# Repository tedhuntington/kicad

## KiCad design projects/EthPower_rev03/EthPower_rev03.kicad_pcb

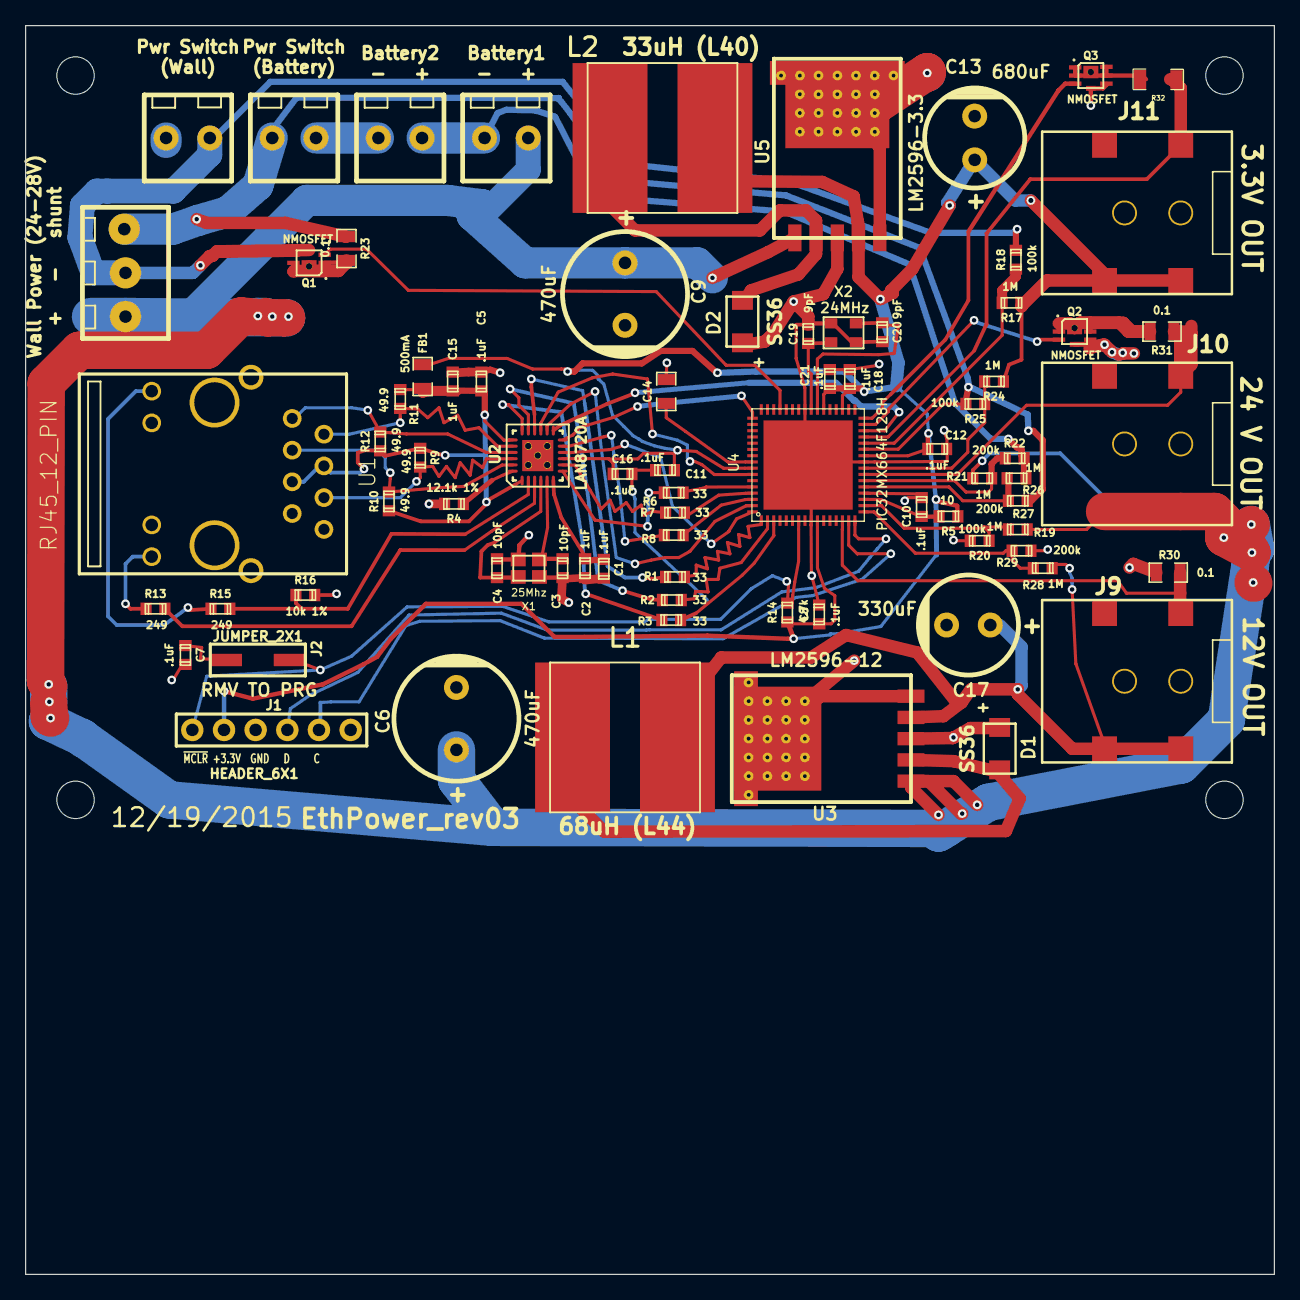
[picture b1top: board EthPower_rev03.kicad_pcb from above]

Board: 2 copper layers, 100.0 x 100.0 mm, 82 parts (0 on the bottom side), 63 nets.

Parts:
C1, C5, C7, C8, C10, C11, C12, C16, C18, C21: .1uF; TED_SM0603_C
C2, C15: 1uF; TED_SM0603_C
C3, C4: 10pF; TED_SM0603_C
C6, C9: 470uF; TED_c_elec_radial_10mm
C13: 680uF; TED_c_elec_radial_8mm
C14: 10uF (low ESR 1ohm); TED_SM0805_C
C17: 330uF; TED_c_elec_radial_8mm
C19, C20: 9pF; TED_SM0603_C
D1, D2: SS36; TED_DO-214AC
FB1: 500mA; TED_SM0805_R
H1, H2, H3, H4: HOLE; TED_Hole_3mm
J1: HEADER_6X1; TED_HEADER_6x1
J2: JUMPER_2X1; TED_HEADER_2x1_SMT
J3, J5, J6, J7: TERMINAL_2X1; TED_TERMINAL_3.5MM_2PIN
J8: TERMINAL_3X1; TED_TERMINAL_3.5MM_3PIN
J9, J10, J11: DC_2.1MM; TED_2.1mm_DC_SMD
L1: 68uH (L44); INDUCTOR_12x12_SMD
L2: 33uH (L40); INDUCTOR_12x12_SMD
Q1, Q2, Q3: NMOSFET; TED_PQFN6+1
R1, R2, R3, R6, R7, R8: 33; TED_SM0603_R
R4: 12.1k 1%; TED_SM0603_R
R5: 10; TED_SM0603_R
R9, R10, R11, R12: 49.9; TED_SM0603_R
R13, R15: 249; TED_SM0603_R
R14: 4.7k; TED_SM0603_R
R16: 10k 1%; TED_SM0603_R
R17, R19, R21, R24, R26, R28: 1M; TED_SM0603_R
R18, R20, R25: 100k; TED_SM0603_R
R22, R27, R29: 200k; TED_SM0603_R
R23, R30, R31: 0.1; TED_SM0805_R
R32: 0.1; TED_SM1206_R
U1: RJ45_12_PIN; TED_RJ45_12pin_Top
U2: LAN8720A; TED_QFN24+1
U3: LM2596-12; TED_TO263
U4: PIC32MX664F128H; TED_QFN64+1
U5: LM2596-3.3; TED_TO263
X1: 25Mhz; TED_crystal_FA-20H
X2: 24MHz; crystal_TSX3225

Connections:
12V: C17.1, J9.1, L1.2, R28.1, U3.4
AVDD: C5.1, C15.1, FB1.2, R9.1, R10.1, R11.1, R12.1, U1.4, U1.5, U2.1, U2.19
ECRSDV: R8.2, U4.62
EMDC: U2.13, U4.30
EMDIO: U2.12, U4.49
EREFCLK: U2.14, U4.63
ERXD0: R7.2, U4.61
ERXD1: R6.2, U4.60
ERXERR: U2.10, U4.64
ETXD0: R2.2, U4.2
ETXD1: R3.2, U4.3
ETXEN: R1.2, U4.1
GND: C1.2, C2.2, C3.2, C4.1, C5.2, C6.2, C7.2, C8.2, C9.2, C10.2, C11.2, C12.2, C13.2, C14.2, C15.2, C16.2, C17.2, C18.2, C19.2, C20.2, C21.2, D1.2, D2.2, J1.3, J5.1, Q2.2, Q3.2, R4.2, R16.2, R20.2, R29.2, R30.2, U1.8, U1.10, U1.11, U2.25, U3.3, U3.5, U4.9, U4.20, U4.25, U4.41, U4.65, U5.3, U5.5, X1.2, X1.4, X2.2, X2.4
GNDWALL: J5.2, J8.2, Q1.2, R18.2
GreenLED: R15.1, U1.9
unnamed: C1.1, C2.1, U2.6
unnamed: C3.1, U2.5, X1.1
unnamed: C4.2, U2.4, X1.3
unnamed: C7.1, J2.1
unnamed: C10.1, R5.2, U4.19
unnamed: C19.1, U4.40, X2.1
unnamed: C20.1, U4.39, X2.3
unnamed: D1.1, L1.1, U3.2
unnamed: D2.1, L2.1, U5.2
unnamed: J3.1, J6.2
unnamed: Q1.3, R23.2
unnamed: Q2.3, R31.2
unnamed: Q3.3, R32.2
unnamed: R1.1, U2.16
unnamed: R2.1, U2.17
unnamed: R3.1, U2.18
unnamed: R4.1, U2.24
unnamed: R6.1, U2.7
unnamed: R7.1, U2.8
unnamed: R8.1, U2.11
unnamed: R13.2, U2.3
unnamed: R15.2, R16.1, U2.2
PGEC1_RB1: J1.5, U4.15
PGED1_RB0: J1.4, U4.16
RXN: R9.2, U1.6, U2.22
RXP: R10.2, U1.3, U2.23
SenseBatteryConnected: R24.2, R25.1, U4.24
SenseCurrent3.3v: J11.2, R32.1, U4.29
SenseCurrent12v: J9.2, R30.1, U4.14
SenseCurrent24v: J10.2, R31.1, U4.23
SenseCurrentCharger/GNDBATTERY: J6.1, J8.3, R23.1, R25.2, R27.2, U4.27
SenseVolt12VOut: R28.2, R29.1, U4.17
SenseVoltBattery1: R21.2, R22.1, U4.22
SenseVoltBattery2: R26.2, R27.1, U4.21
SenseVoltFull: R19.2, R20.1, U4.18
SenseWallConnected: R17.2, R18.1, U4.28
Switch3.3V: Q3.1, U4.32
Switch24V: Q2.1, U4.31
SwitchCharger: Q1.1, U4.45
TXN: R11.2, U1.2, U2.20
TXP: R12.2, U1.1, U2.21
VBat2: J3.2, J7.1, R22.2, R26.1
VCAP: C14.1, U4.56
VDD: C8.1, C11.1, C12.1, C13.1, C16.1, C18.1, C21.1, FB1.1, J1.2, J11.1, L2.2, R5.1, R14.1, R17.1, R24.1, U2.9, U4.10, U4.26, U4.35, U4.38, U4.57, U5.4
VWallVBat: C6.1, C9.1, J7.2, J8.1, J10.1, R19.1, R21.1, U3.1, U5.1
YellowLED: R13.1, U1.12
nRST: U2.15, U4.58
~MCLR~: J1.1, J2.2, R14.2, U4.7

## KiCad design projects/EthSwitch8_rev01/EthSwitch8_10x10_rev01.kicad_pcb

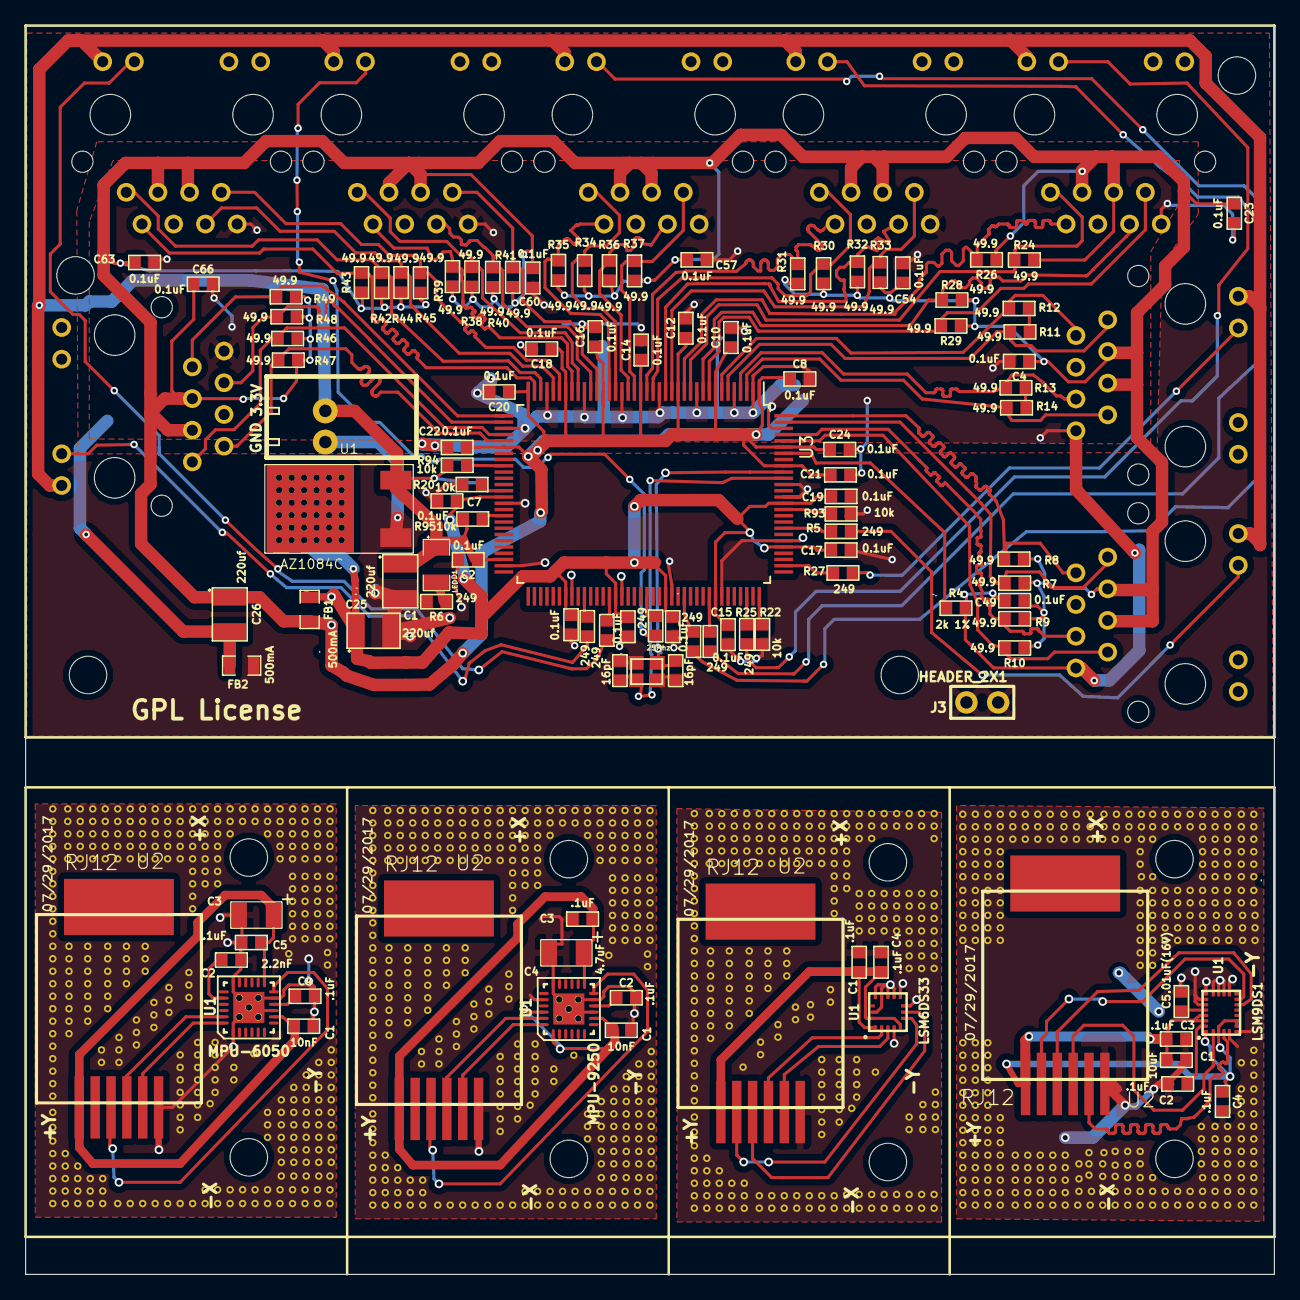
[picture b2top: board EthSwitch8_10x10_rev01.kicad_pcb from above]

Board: 2 copper layers, 100.0 x 100.0 mm, 130 parts (0 on the bottom side), 86 nets.

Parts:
C1, C25, C26: 220uf; TED_SM3528_1311_ELEC_C
C1#2, C1#3: 10nF; TED_SM0603_C
C1#4, C2#3, C2#4, C3#2, C3#3, C4#2, C4#4, C4#5, C5: .1uF; TED_SM0603_C
C1#5: 10uF; TED_SM0603_C
C2, C4, C7, C8, C9, C10, C11, C12, C13, C14, C15, C16, C17, C18, C19, C20, C21, C22, C23, C24, C49, C54, C57, C60, C63, C66: 0.1uF; TED_SM0603_C
C2#2: 2.2nF; TED_SM0603_C
C3, C4#3: 4.7uF; TED_SM3216_1206_ELEC_C
C5#2: .01uF(16V); TED_SM0603_C
C47, C48: 16pF; TED_SM0603_C
D1: LED; TED_SM1206_LED
FB1, FB2: 500mA; TED_SM0805_R
H1, H1#2, H1#3, H1#4, H1#5, H2, H2#2, H2#3, H2#4, H2#5, H3, H4: HOLE; TED_Hole_3mm
J1: Terminal_2x1; TED_TERMINAL_SPRING_2.54MM_2PIN_1989748
J3: HEADER_2X1; TED_HEADER_2x1
R4: 2k 1%; TED_SM0603_R
R5, R6, R15, R17, R19, R21, R23, R25, R27: 249; TED_SM0603_R
R7, R8, R9, R10, R11, R12, R13, R14, R24, R26, R28, R29, R30, R31, R32, R33, R34, R35, R36, R37, R38, R39, R40, R41, R42, R43, R44, R45, R46, R47, R48, R49: 49.9; TED_SM0603_R
R20, R22, R93, R94, R95: 10k; TED_SM0603_R
U1: AZ1084C; TED_TO252-2
U1#2: MPU-6050; TED_QFN24+1_NO_PASTE
U1#3: MPU-9250; TED_QFN24+1
U1#4: LSM6DS33; LGA-16
U1#5: LSM9DS1; LGA-24
U2, U2#2, U2#3, U2#4: RJ12; TED_RJ12_855135002
U3: RTL8309SB_PQFP; LQFP-128_14x20mm_Pitch0.5mm
U4, U5, U6, U7, U8, U9, U10, U11: RJ45_12_PIN_UP; TED_RJ45_12pin_Up_Bottom
X1: 25Mhz; TED_crystal_FA-20H

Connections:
AGND: C4.2, C8.2, C10.2, C12.2, C14.2, C16.2, C18.2, C20.2, C21.2, C22.2, C23.2, C24.2, C26.2, C49.2, C54.2, C57.2, C60.2, C63.2, C66.2, FB2.2, R4.2, U3.2, U3.5, U3.11, U3.17, U3.23, U3.29, U3.35, U3.41, U3.126, U4.8, U5.8, U6.8, U7.8, U8.8, U9.8, U10.8, U11.8
GND: C1.2, C1#2.2, C1#3.2, C1#4.2, C1#5.2, C2.2, C2#2.2, C2#3.2, C2#4.2, C3.2, C3#2.2, C3#3.2, C4#2.2, C4#3.2, C4#4.2, C4#5.2, C5.2, C5#2.2, C7.2, C9.2, C11.2, C13.2, C15.2, C17.2, C19.2, C25.2, C47.1, C48.2, FB2.1, J1.2, J3.1, J3.2, R6.2, R20.2, R22.2, R93.1, U1.1, U1#2.1, U1#2.9, U1#2.11, U1#2.18, U1#2.25, U1#3.9, U1#3.11, U1#3.18, U1#3.20, U1#3.25, U1#4.4, U1#4.8, U1#4.9, U1#4.10, U1#4.11, U1#4.12, U1#4.13, U1#4.15, U1#5.5, U1#5.6, U1#5.14, U1#5.15, U1#5.16, U1#5.17, U1#5.18, U1#5.19, U1#5.20, U2.1, U2#2.1, U2#3.1, U2#4.1, U3.53, U3.63, U3.72, U3.80, U3.88, U3.96, U3.108, U3.115, U3.117, X1.2, X1.4
GreenLED0: R5.2, U4.10
GreenLED1: R27.2, U5.10
GreenLED2: R25.2, U6.10
GreenLED3: R23.2, U7.10
GreenLED4: R21.2, U8.10
GreenLED5: R19.2, U9.10
GreenLED6: R17.2, U10.10
GreenLED7: R15.2, U11.10
INT: U1#2.12, U1#3.12, U2.4, U2#2.4
INT1: U1#4.7, U1#5.11, U2#3.4, U2#4.4
INT2: U1#4.6, U1#5.12, U2#3.5, U2#4.5
unnamed: C2#2.1, C2#3.1, C2#4.1, U1#2.20, U1#3.10, U1#5.24
unnamed: C4#2.1, U1#2.10
unnamed: C5#2.1, U1#5.21
unnamed: D1.2, R6.1
unnamed: R4.1, U3.122
unnamed: R5.1, U3.110
unnamed: R11.2, R12.1
unnamed: R13.2, R14.1
unnamed: R15.1, U3.74
unnamed: R17.1, U3.78
unnamed: R19.1, U3.84
unnamed: R20.1, U3.51
unnamed: R21.1, U3.90
unnamed: R22.1, U3.102
unnamed: R23.1, U3.94
unnamed: R25.1, U3.100
unnamed: R27.1, U3.104
unnamed: R93.2, U3.113
unnamed: R94.2, U3.47
unnamed: R95.2, U3.55
unnamed: U1#2.2, U1#3.2
unnamed: U1#2.3, U1#3.3
unnamed: U1#2.4, U1#3.4
unnamed: U1#2.5, U1#3.5
unnamed: U1#2.6, U1#3.6
unnamed: U1#2.7, U1#3.7
unnamed: U1#2.14, U1#3.14, U1#4.14
unnamed: U1#2.15, U1#3.15
unnamed: U1#2.16, U1#3.16
unnamed: U1#2.17, U1#3.17
unnamed: U1#2.19, U1#3.19
unnamed: U1#2.21, U1#3.21
unnamed: U2.5, U2#2.5
RXN0: R10.2, U3.124, U4.7
RXN1: R14.2, U3.3, U5.7
RXN2: R29.2, U3.9, U6.7
RXN3: R33.2, U3.15, U7.7
RXN4: R37.2, U3.21, U8.7
RXN5: R41.2, U3.27, U9.7
RXN6: R45.2, U3.33, U10.7
RXN7: R49.2, U3.39, U11.7
RXP0: R9.1, U3.125, U4.6
RXP1: R13.1, U3.4, U5.6
RXP2: R28.1, U3.10, U6.6
RXP3: R32.1, U3.16, U7.6
RXP4: R36.1, U3.22, U8.6
RXP5: R40.1, U3.28, U9.6
RXP6: R44.1, U3.34, U10.6
RXP7: R48.1, U3.40, U11.6
SCL: U1#2.23, U1#3.23, U1#4.2, U1#5.2, U2.3, U2#2.3, U2#3.3, U2#4.3
SDA: U1#2.24, U1#3.24, U1#4.3, U1#5.4, U2.2, U2#2.2, U2#3.2, U2#4.2
TXN0: R8.2, U3.128, U4.2
TXN1: R12.2, U3.7, U5.2
TXN2: R26.2, U3.13, U6.2
TXN3: R31.2, U3.19, U7.2
TXN4: R35.2, U3.25, U8.2
TXN5: R39.2, U3.31, U9.2
TXN6: R43.2, U3.37, U10.2
TXN7: R47.2, U3.43, U11.2
TXP0: R7.1, U3.127, U4.1
TXP1: R11.1, U3.6, U5.1
TXP2: R24.1, U3.12, U6.1
TXP3: R30.1, U3.18, U7.1
TXP4: R34.1, U3.24, U8.1
TXP5: R38.1, U3.30, U9.1
TXP6: R42.1, U3.36, U10.1
TXP7: R46.1, U3.42, U11.1
VDDA: C4.1, C8.1, C10.1, C12.1, C14.1, C16.1, C18.1, C20.1, C21.1, C22.1, C23.1, C24.1, C26.1, C49.1, C54.1, C57.1, C60.1, C63.1, C66.1, FB1.2, R7.2, R8.1, R9.2, R10.1, R24.2, R26.1, R28.2, R29.1, R30.2, R31.1, R32.2, R33.1, R34.2, R35.1, R36.2, R37.1, R38.2, R39.1, R40.2, R41.1, R42.2, R43.1, R44.2, R45.1, R46.2, R47.1, R48.2, R49.1, U3.1, U3.8, U3.14, U3.20, U3.26, U3.32, U3.38, U3.44, U3.120, U3.123, U4.3, U4.5, U5.3, U5.5, U6.3, U6.5, U7.3, U7.5, U8.3, U8.5, U9.3, U9.5, U10.3, U10.5, U11.3, U11.5
VDDD: C7.1, C9.1, C11.1, C13.1, C15.1, C17.1, C19.1, C25.1, FB1.1, U1.2, U3.52, U3.71, U3.79, U3.87, U3.95, U3.107, U3.114
VDDIO: C1.1, C2.1, D1.1, J1.1, R94.1, R95.1, U1.3, U3.62, U4.9, U5.9, U6.9, U7.9, U8.9, U9.9, U10.9, U11.9
Vdd: C1#2.1, C1#3.1, C1#4.1, C1#5.1, C3.1, C3#2.1, C3#3.1, C4#3.1, C4#4.1, C4#5.1, C5.1, U1#2.8, U1#2.13, U1#3.1, U1#3.8, U1#3.13, U1#3.22, U1#4.1, U1#4.5, U1#4.16, U1#5.1, U1#5.3, U1#5.7, U1#5.8, U1#5.22, U1#5.23, U2.6, U2#2.6, U2#3.6, U2#4.6
X1: C48.1, U3.118, X1.1
X2: C47.2, U3.119, X1.3

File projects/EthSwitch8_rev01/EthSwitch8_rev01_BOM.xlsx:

EthSwitch8_rev01
Sun 23 Jul 2017 09:28:10 AM PDT
Eeschema 4.0.6-e0-6349~53~ubuntu16.04.1
Component Count:112
Ref | Qnty | Value | Part | Part# | Unit Cost | Total Cost | Major Distributor | Minor Distributor
C26, C25, C1, | 3 | 220uf | capacitors:SM3528_1311_ELEC_C | TMCMB0J227MTRF | 0.5 | 1.5 | Mouser
C47, C48, | 2 | 16pF | capacitors:SM0603_C | GRM1885C1H160JA01D | 0.1 | 0.2 | Mouser
C8, C10, C12, C14, C16, C18, C20, C22, C24, C7, C9, C11, C13, C15, C17, C19, C2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 | 26 | 0.1uF | capacitors:SM0603_C | Vj0603V104ZXAPW1BC | 0.1 | 2.6 | Mouser
D1, | 1 | LED | led:SM1206_LED | APTR3216SGC | 0.15 | 0.15 | Mouser
FB1, FB2, | 2 | 500mA | resistors:SM0805_R | MPZ2012S601A | 0.12 | 0.24 | Mouser
H1, H2, H3, H4, | 4 | HOLE | holes:Hole_3mm |  | 0 | 0
J1, | 1 | Terminal_2x1 | connectors:TERMINAL_SPRING_2.54MM_2PIN_1989748 | 1989748 | 0.28 | 0.28 | Mouser
J2, J3, | 2 | HEADER_2X1 | connectors:HEADER_2x1 | FCI 68000-102HLF | 0.19 | 0.38 | Digi-Key
P1, P2, P3, P4, P5, P6, P7, P8, P9, P10, P11, P12, P13, | 13 | TEST_PAD | test_pads:TEST_PAD |  | 0 | 0
R10, R9, R7, R8, R14, R13, R11, R12, R29, R28, R24, R26, R33, R32, R30, R31, R3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 | 32 | 49.9 | resistors:SM0603_R | ERJ-3EKF49R9V | 0.1 | 3.2 | Digi-Key
R22, R20, R94, R93, R95, | 5 | 10k | resistors:SM0603_R | ERJ-3EKF1001V | 0.1 | 0.5 | Digi-Key
R4, | 1 | 2k 1% | resistors:SM0603_R | RC0603FR-072KL | 0.1 | 0.1 | Digi-Key/Mouser
R6, R5, R27, R25, R23, R21, R19, R17, R15, | 9 | 249 | resistors:SM0603_R | ERJ-2RKF2490X | 0.1 | 0.9 | Digi-Key/Mouser
U1, | 1 | AZ1084C | regulators:TO252-2 | AZ1084C | 0.65 | 0.65 | Mouser
U3, | 1 | RTL8309SB_PQFP |  | RTL8309SB | 1.6 | 1.6 |  | AliExpress
U4, U6, U8, U10, U7, U9, U11, U5, | 8 | RJ45_12_PIN_UP | connectors:RJ45_12pin_Up_Bottom | HY951180A | 0.88 | 7.04 |  | AliExpress
X1, | 1 | 25Mhz | crystals:crystal_FA-20H | FA-20H 25.0000MF20X-K3 | 0.73 | 0.73 | Mouser
 |  |  |  |  |  | 20.07

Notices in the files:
projects/EthSwitch8_rev01/EthSwitch8_10x10_rev01.kicad_pcb:
GPL License
